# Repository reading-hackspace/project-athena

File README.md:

# Project Athena

A simple project to build and learn electronics and embedded design at rLab

## Objectives:
<ul>
<li>Develop individual and shared electronic design skills</li>
<li>Learn PCB design and build techniques with Kicad and external PCB manufacturers</li>
<li>Improve surface mount and through hole soldering skills</li>
<li>Familiarise members with rLab electronics tools, equipment, and knowledge</li>
<li>Make a fun device</li>
</ul>

## Design Specification
Derived from the previous 555 Synth Punk construction project
<ul>
<li>design should be Microprocessor based rather than 555</li>
<li>It should have a keyboard. This could be buttons, stylophone, touch sensor, or other. Probably single octave.</li>
<li>Cost components and board under £10</li>
<li>Improved Audio output using proper amplifier IC and board mounted speaker, possibly I2S codec</li>
<li>A couple of knobs and buttons to change sound settings</li>
<li>USB powered</li>
<li>Audio output jack</li>
<li>Mixture of surface mount and through hole components</li>
<li>LCD display integral</li> 
<li>Expansion connector to add new personalised features</li>v
<li>C++ or Python programming.</li>
</ul>

## Design Approach
The design is built of modules which can be independently sourced, designed and prototyped before integration into a complete design.

## Proposed Modules
The following modules are proposed to be in the design, being available and at reasonable cost:

### Raspberry Pi Pico Processor Module

The Raspberry Pi Pico module is based on the RP2040 microprocessor. The module includes flash memory, power supply, crystal clock and a USB interface. It is an easy way to to integrate this processor without detail PCB layout and at attractive cost.
The Pi Pico Module have different variants which are pin compatible. They offer different USB Connectors(Micro-B, USB-C), Wireless and bluetooth integrated, and a higher performance version in the RP2350.
[Pi Pico Data sheet](https://datasheets.raspberrypi.com/pico/pico-datasheet.pdf)

The RP2040 is an ARM Cortex M0+ 32 bit processor which operates at 133MHz and includes a wide range of integrated peripherals.
[RP2040 Data sheet](https://datasheets.raspberrypi.com/rp2040/rp2040-datasheet.pdf)

High quality software support for the RP2040 and Pi Pico Modules is available in C/C++ ([C SDK](https://www.raspberrypi.com/documentation/microcontrollers/c_sdk.html), and [Arduino Pi Pico](https://www.tomshardware.com/how-to/program-raspberry-pi-pico-with-arduino-ide)), and Python([Micropython](https://www.raspberrypi.com/documentation/microcontrollers/micropython.html), and [CircuitPython](https://circuitpython.org/board/raspberry_pi_pico/))

### Capacitive touch Music Keyboard

A number of different keyboard switch types were considered including push butttons, stylophone type stylus and capacitive touch. The later was chosen for simplicity and the capability to play chords with multiple notes simultaneously.

A few different alternatives for the capacitive touch keyboard layout and interface were tested. The keyboard was prototyped with copper tape covered in kapton tape to simulate the PCB pads and solder mask in the final PCB. The Pi Pico does support direct connection of GPIO pins to interface capacitive touch switches using the CircuitPython [touchio library](https://docs.circuitpython.org/en/latest/shared-bindings/touchio/index.html), However it uses a lot of GPIO pins for a 12 key keyboard. It was decided to us a specialised Capacitive touch chip with and I2C interface [MPR121](https://www.nxp.com/docs/en/data-sheet/MPR121.pdf). This chip is very small and will present a good challenge in construction, however it is available already mounted on low cost modules for prototyping. The chip supports up to 4 different I2C addresses allowing additional octave to be added.

### PWM Audio Output
The Pi Pico supports PWM output to a GPIO pin for audio tone output. The resulting output is rather noisy as described in section 3.4.1 of the  [RP2040 hardware interface manual](https://datasheets.raspberrypi.com/rp2040/hardware-design-with-rp2040.pdf). It was chosen to implement the low noise 3.3V audio supply, the buffer, and the filter circuit.

### I2S Audio Codec
In addition to the PWM a I2S audio DAC is included for higher quality stereo output. The [PCM5102 DAC](https://www.ti.com/lit/ds/symlink/pcm5102.pdf) analog part is also powered from the low noise 3.3V supply

### Audio Amplifier and Loudspeaker

Low cost audio power amplifiers with 1W output power baaed on the LM386 are available. [LM386 module](https://www.switchelectronics.co.uk/products/lm386-audio-amplifier-board-200-gain-amplifier-module-power)

The LM386 IC can operate with few external components with a gain of 20 which is suitable for our application.[LM386 Data sheet](https://www.ti.com/lit/ds/symlink/lm386.pdf)

The loudspeaker is proposed to be board mounted.[30mm Loudspeaker](https://proto-pic.co.uk/product/speaker-30mm-dia-8-ohm-pcb-mounted)

Audio Output to an external amplifier is provided via a 3.5mm stereo jack.

### 1.3 inch IPS Colour LCD Display

A colour LCD display was chosen for the device. Limited space allows for a [240 by 240 pixel 1.3 inch IPS display](https://www.smart-prototyping.com/1_3-inch-TFT-IPS-Display-Module-ST7789-SPI-240-240).
The module is based on the ST7789 display IC and is supported by both Micropython and CircuitPython grahics libraries.

### Buttons and Potentiometers.

To interact with the device and display, two potentiometers and six push buttons are included.

### General Purpose Inputs and Outputs.

The board provides spare GPIO connections and power supplies on 2.54mm female headers for external experimental devices. The I2c Bus is also brought out to a connectors to daisy chain octaves or add other I2C devices. The connectors can be male or female and mounted vertically or horizontally on the board

##   Estimated Costs
Derived from Kicad BOM. All including VAT and shipping.
<ul>
<li> PCB, 2 layer 100mm * 100mm JLCPCB      £0.75</li>
<li> Pi Pico 2040 module with micro USB     £1.75</li>
<li> 1.3in LCD Display 240 * 240 pixel      £1.75</li>
<li> Integrated circuits                    £1.25</li>
<li> Connectors                             £0.75</li>
<li> Buttons, Potentiometers                £0.50</li>

<li> Resistors, capacitors                  £0.75</li>
</ul>
Total: 

## PCB Files

## Software

The software is in early stage of test and development. The following capabilities have been tested:
<ul>
<li> Display colour rLab logo on LCD display in Circuit Python
<li> SImple one octave piano with output to internal speaker
<li> Polyphonic synthesiser with output via audio codec
<li> Nintendo style games (Tetris, Flappy Bird) with display and sound
<ul>

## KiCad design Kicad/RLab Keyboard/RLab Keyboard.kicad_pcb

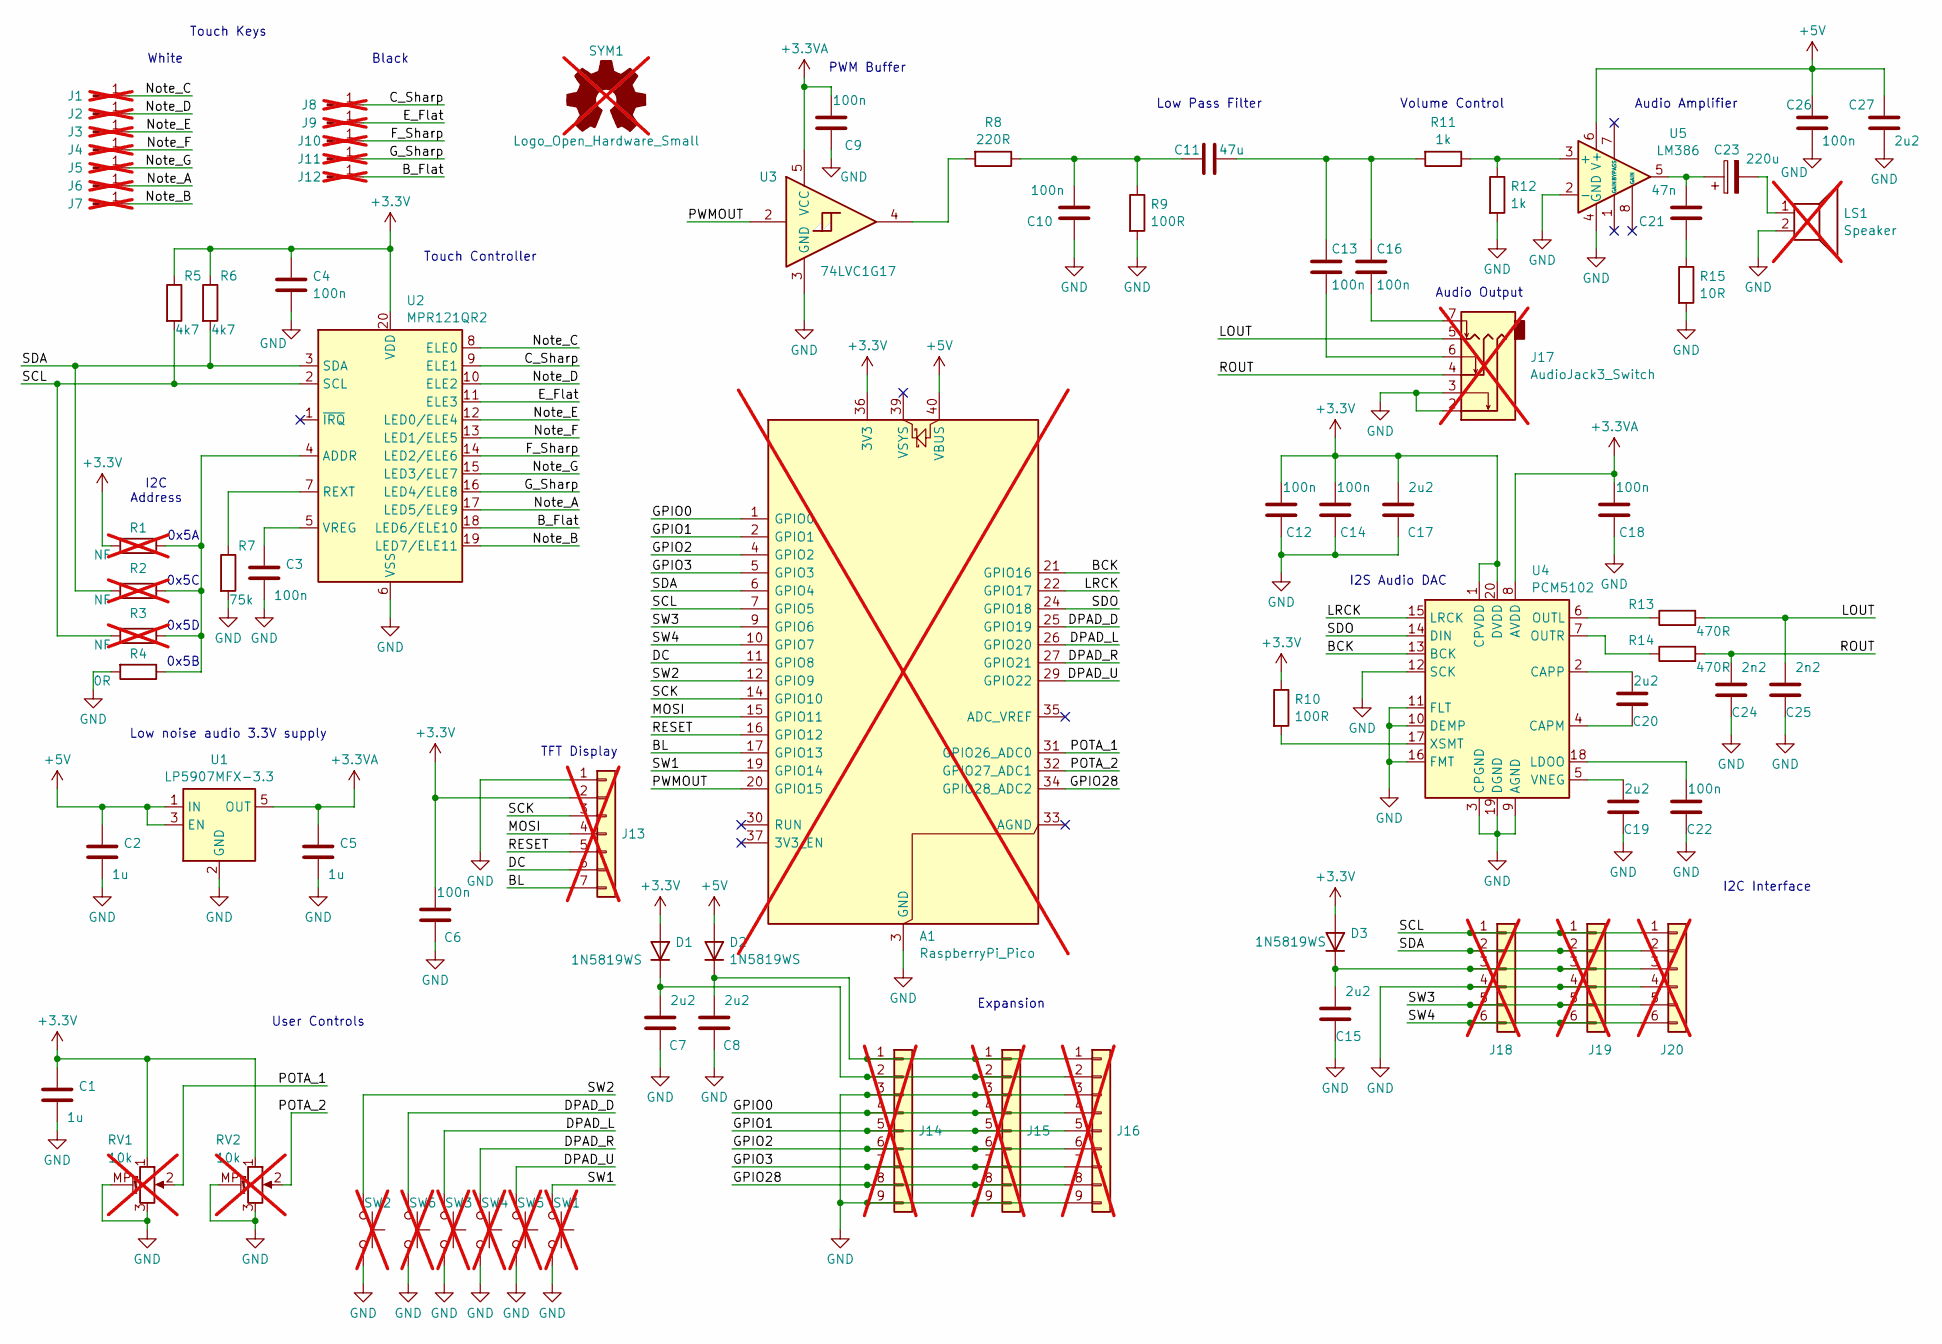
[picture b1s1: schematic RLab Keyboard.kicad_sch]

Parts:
A1: RaspberryPi_Pico; RPi_Pico_SMD_TH; not fitted
C1, C2, C5: 1u; C_0603_1608Metric; LCSC Part C111590
C3, C4, C6, C9, C10, C12, C13, C14, C16, C18, C22, C26: 100n; C_0603_1608Metric; LCSC Part C6119867
C7, C8, C15, C17, C19, C20, C27: 2u2; C_0603_1608Metric; LCSC Part C5189830
C11: 47u; C_0805_2012Metric; LCSC Part C19103846
C21: 47n; C_0603_1608Metric; LCSC Part C597218
C23: 220u; C_1206_3216Metric; LCSC Part C412252
C24, C25: 2n2; C_0603_1608Metric; LCSC Part C1604
D1, D2, D3: 1N5819WS; D_SOD-323; LCSC Part C191023
J1, J2, J3, J4, J5, J6, J7: Conn_01x01_Pin; White_Key; not fitted
J8, J9, J10, J11, J12: Conn_01x01_Pin; Black_key_fill; not fitted
J13: Conn_01x07; 240LCD; not fitted
J14: Conn_01x09; PinHeader_1x09_P2.54mm_Horizontal; not fitted
J15: Conn_01x09; PinSocket_1x09_P2.54mm_Vertical; not fitted
J16: Conn_01x09; PinSocket_1x09_P2.54mm_Horizontal; not fitted
J17: AudioJack3_Switch; Jack_3.5mm_PJ342_Horizontal; LCSC Part C668606; not fitted
J18: Conn_01x06; PinSocket_1x06_P2.54mm_Horizontal; not fitted
J19: Conn_01x06; PinHeader_1x06_P2.54mm_Horizontal; not fitted
J20: Conn_01x06; PinSocket_1x06_P2.54mm_Vertical; not fitted
LS1: Speaker; 30mm_Speaker; not fitted
R1, R2, R3: NF; R_0603_1608Metric; not fitted
R4: 0R; R_0603_1608Metric; LCSC Part C95177
R5, R6: 4k7; R_0603_1608Metric; LCSC Part C99782
R7: 75k; R_0603_1608Metric; LCSC Part C114636
R8: 220R; R_0603_1608Metric; LCSC Part C107696
R9, R10: 100R; R_0603_1608Metric; LCSC Part C105588
R11, R12: 1k; R_0603_1608Metric; LCSC Part C22548
R13, R14: 470R; R_0603_1608Metric; LCSC Part C114669
R15: 10R; R_0603_1608Metric; LCSC Part C22859
RV1, RV2: 10k; Potentiometer_Alps_RK09K_Single_Vertical; not fitted
SW1, SW2, SW3, SW4, SW5, SW6: SW_MEC_5G; SW_PUSH_6mm_H8mm; not fitted
SYM1: Logo_Open_Hardware_Small; OSHW-Logo_11.4x12mm_SilkScreen; not fitted
U1: LP5907MFX-3.3; SOT-23-5; LCSC Part C5370990
U2: MPR121QR2; UQFN-20_3x3mm_P0.4mm; LCSC Part C91322
U3: 74LVC1G17; SOT-353_SC-70-5; LCSC Part C19829654
U4: PCM5102; TSSOP-20_4.4x6.5mm_P0.65mm; LCSC Part C107671
U5: LM386; SOIC-8_3.9x4.9mm_P1.27mm; LCSC Part C22438596

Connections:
+3.3V: A1.36 (3V3), C1.1, C4.1, C6.2, C12.2, C14.2, C17.2, D1.2 (A), D3.2 (A), J13.2, R1.2, R5.1, R6.1, R10.1, RV1.1, RV2.1, U2.20 (VDD), U4.1 (CPVDD), U4.20 (DVDD)
+3.3VA: C5.1, C9.2, C18.2, U1.5 (OUT), U3.5 (VCC), U4.8 (AVDD)
+5V: A1.40 (VBUS), C2.1, C26.1, C27.2, D2.2 (A), U1.1 (IN), U1.3 (EN), U5.6 (V+)
/BCK: A1.21 (GPIO16), U4.13 (BCK)
/BL: A1.17 (GPIO13), J13.7
/B_Flat: J12.1, U2.18 (LED6/ELE10)
/C_Sharp: J8.1, U2.9 (ELE1)
/DC: A1.11 (GPIO8), J13.6
/DPAD_D: A1.25 (GPIO19), SW6.1
/DPAD_L: A1.26 (GPIO20), SW3.1
/DPAD_R: A1.27 (GPIO21), SW4.1
/DPAD_U: A1.29 (GPIO22), SW5.1
/E_Flat: J9.1, U2.11 (ELE3)
/F_Sharp: J10.1, U2.14 (LED2/ELE6)
/GPIO0: A1.1 (GPIO0), J14.4, J15.4, J16.4
/GPIO1: A1.2 (GPIO1), J14.5, J15.5, J16.5
/GPIO2: A1.4 (GPIO2), J14.6, J15.6, J16.6
/GPIO3: A1.5 (GPIO3), J14.7, J15.7, J16.7
/GPIO28: A1.34 (GPIO28_ADC2), J14.8, J15.8, J16.8
/G_Sharp: J11.1, U2.16 (LED4/ELE8)
/LOUT: C25.2, J17.5, R13.2
/LRCK: A1.22 (GPIO17), U4.15 (LRCK)
/MOSI: A1.15 (GPIO11), J13.4
/Note_A: J6.1, U2.17 (LED5/ELE9)
/Note_B: J7.1, U2.19 (LED7/ELE11)
/Note_C: J1.1, U2.8 (ELE0)
/Note_D: J2.1, U2.10 (ELE2)
/Note_E: J3.1, U2.12 (LED0/ELE4)
/Note_F: J4.1, U2.13 (LED1/ELE5)
/Note_G: J5.1, U2.15 (LED3/ELE7)
/POTA_1: A1.31 (GPIO26_ADC0), RV1.2
/POTA_2: A1.32 (GPIO27_ADC1), RV2.2
/PWMOUT: A1.20 (GPIO15), U3.2
/RESET: A1.16 (GPIO12), J13.5
/ROUT: C24.2, J17.4, R14.2
/SCK: A1.14 (GPIO10), J13.3
/SCL: A1.7 (GPIO5), J18.1, J19.1, J20.1, R3.2, R5.2, U2.2 (SCL)
/SDA: A1.6 (GPIO4), J18.2, J19.2, J20.2, R2.2, R6.2, U2.3 (SDA)
/SDO: A1.24 (GPIO18), U4.14 (DIN)
/SW1: A1.19 (GPIO14), SW1.1
/SW2: A1.12 (GPIO9), SW2.1
/SW3: A1.9 (GPIO6), J18.5, J19.5, J20.5
/SW4: A1.10 (GPIO7), J18.6, J19.6, J20.6
GND: A1.3 (GND), A1.8 (GND), A1.13 (GND), A1.18 (GND), A1.23 (GND), A1.28 (GND), A1.38 (GND), C1.2, C2.2, C3.2, C4.2, C5.2, C6.1, C7.1, C8.1, C9.1, C10.1, C12.1, C14.1, C15.1, C17.1, C18.1, C19.1, C22.1, C24.1, C25.1, C26.2, C27.1, J13.1, J14.3, J14.9, J15.3, J15.9, J16.3, J16.9, J17.2, J17.3, J18.4, J19.4, J20.4, LS1.2, R4.2, R7.2, R9.2, R12.2, R15.2, RV1.3, RV1.MP (MountPin), RV2.3, RV2.MP (MountPin), SW1.2, SW2.2, SW3.2, SW4.2, SW5.2, SW6.2, U1.2 (GND), U2.6 (VSS), U3.3 (GND), U4.3 (CPGND), U4.9 (AGND), U4.10 (DEMP), U4.11 (FLT), U4.12 (SCK), U4.16 (FMT), U4.19 (DGND), U5.2 (-), U5.4 (GND)
unnamed: C10.2, C11.2, R8.1, R9.1
unnamed: C11.1, C13.1, C16.1, R11.2
unnamed: C13.2, J17.6
unnamed: C16.2, J17.7
unnamed: C21.1, R15.1
unnamed: C21.2, C23.1, U5.5
unnamed: C23.2, LS1.1
unnamed: C7.2, D1.1 (K), J14.2, J15.2, J16.2
unnamed: C8.2, D2.1 (K), J14.1, J15.1, J16.1
unnamed: C15.2, D3.1 (K), J18.3, J19.3, J20.3
unnamed: R8.2, U3.4
unnamed: R1.1, R2.1, R3.1, R4.1, U2.4 (ADDR)
unnamed: R7.1, U2.7 (REXT)
unnamed: C3.1, U2.5 (VREG)
unnamed: C20.1, U4.4 (CAPM)
unnamed: C20.2, U4.2 (CAPP)
unnamed: C22.2, U4.18 (LDOO)
unnamed: R13.1, U4.6 (OUTL)
unnamed: R14.1, U4.7 (OUTR)
unnamed: C19.2, U4.5 (VNEG)
unnamed: R10.2, U4.17 (XSMT)
unnamed: R11.1, R12.1, U5.3 (+)

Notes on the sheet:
PWM Buffer
Black
I2C Address
Touch Keys
Audio Amplifier
0x5C
0x5A
Audio Output
0x5B
TFT Display
Low noise audio 3.3V supply
Volume Control
Low Pass Filter
I2C Interface
Expansion
0x5D
I2S Audio DAC
User Controls
Touch Controller
White

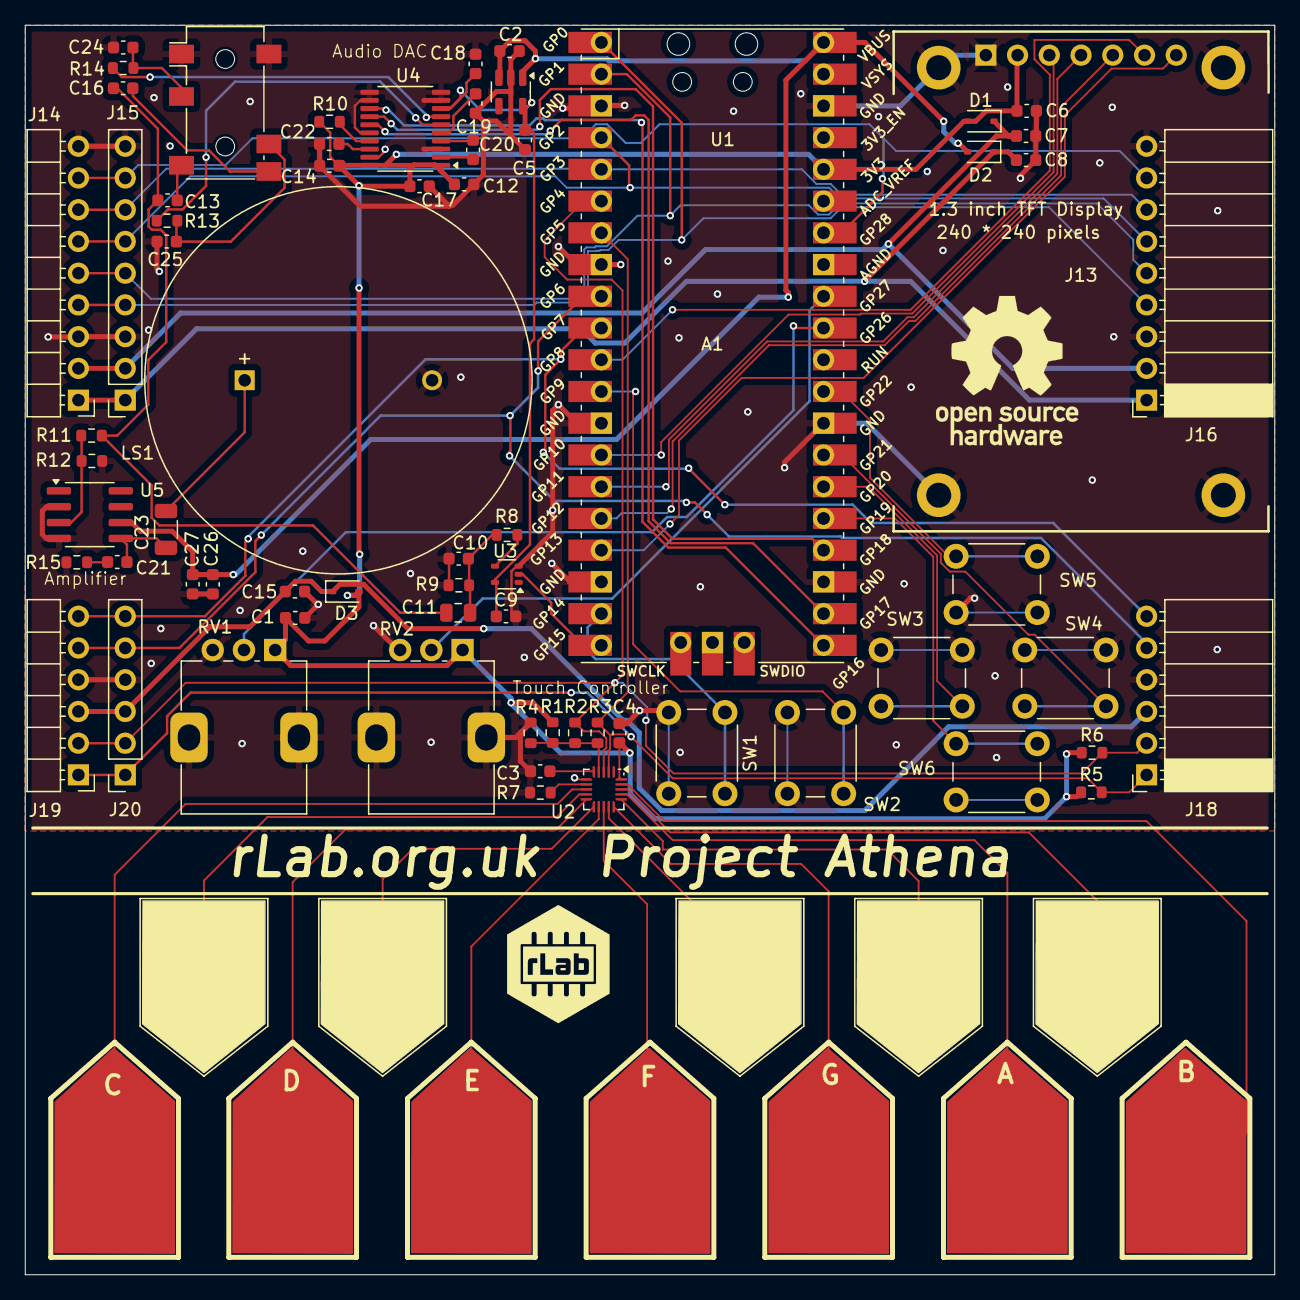
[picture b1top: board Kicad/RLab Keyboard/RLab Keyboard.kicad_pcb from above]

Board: 2 copper layers, 100.0 x 100.0 mm, 81 parts (0 on the bottom side), 66 nets.

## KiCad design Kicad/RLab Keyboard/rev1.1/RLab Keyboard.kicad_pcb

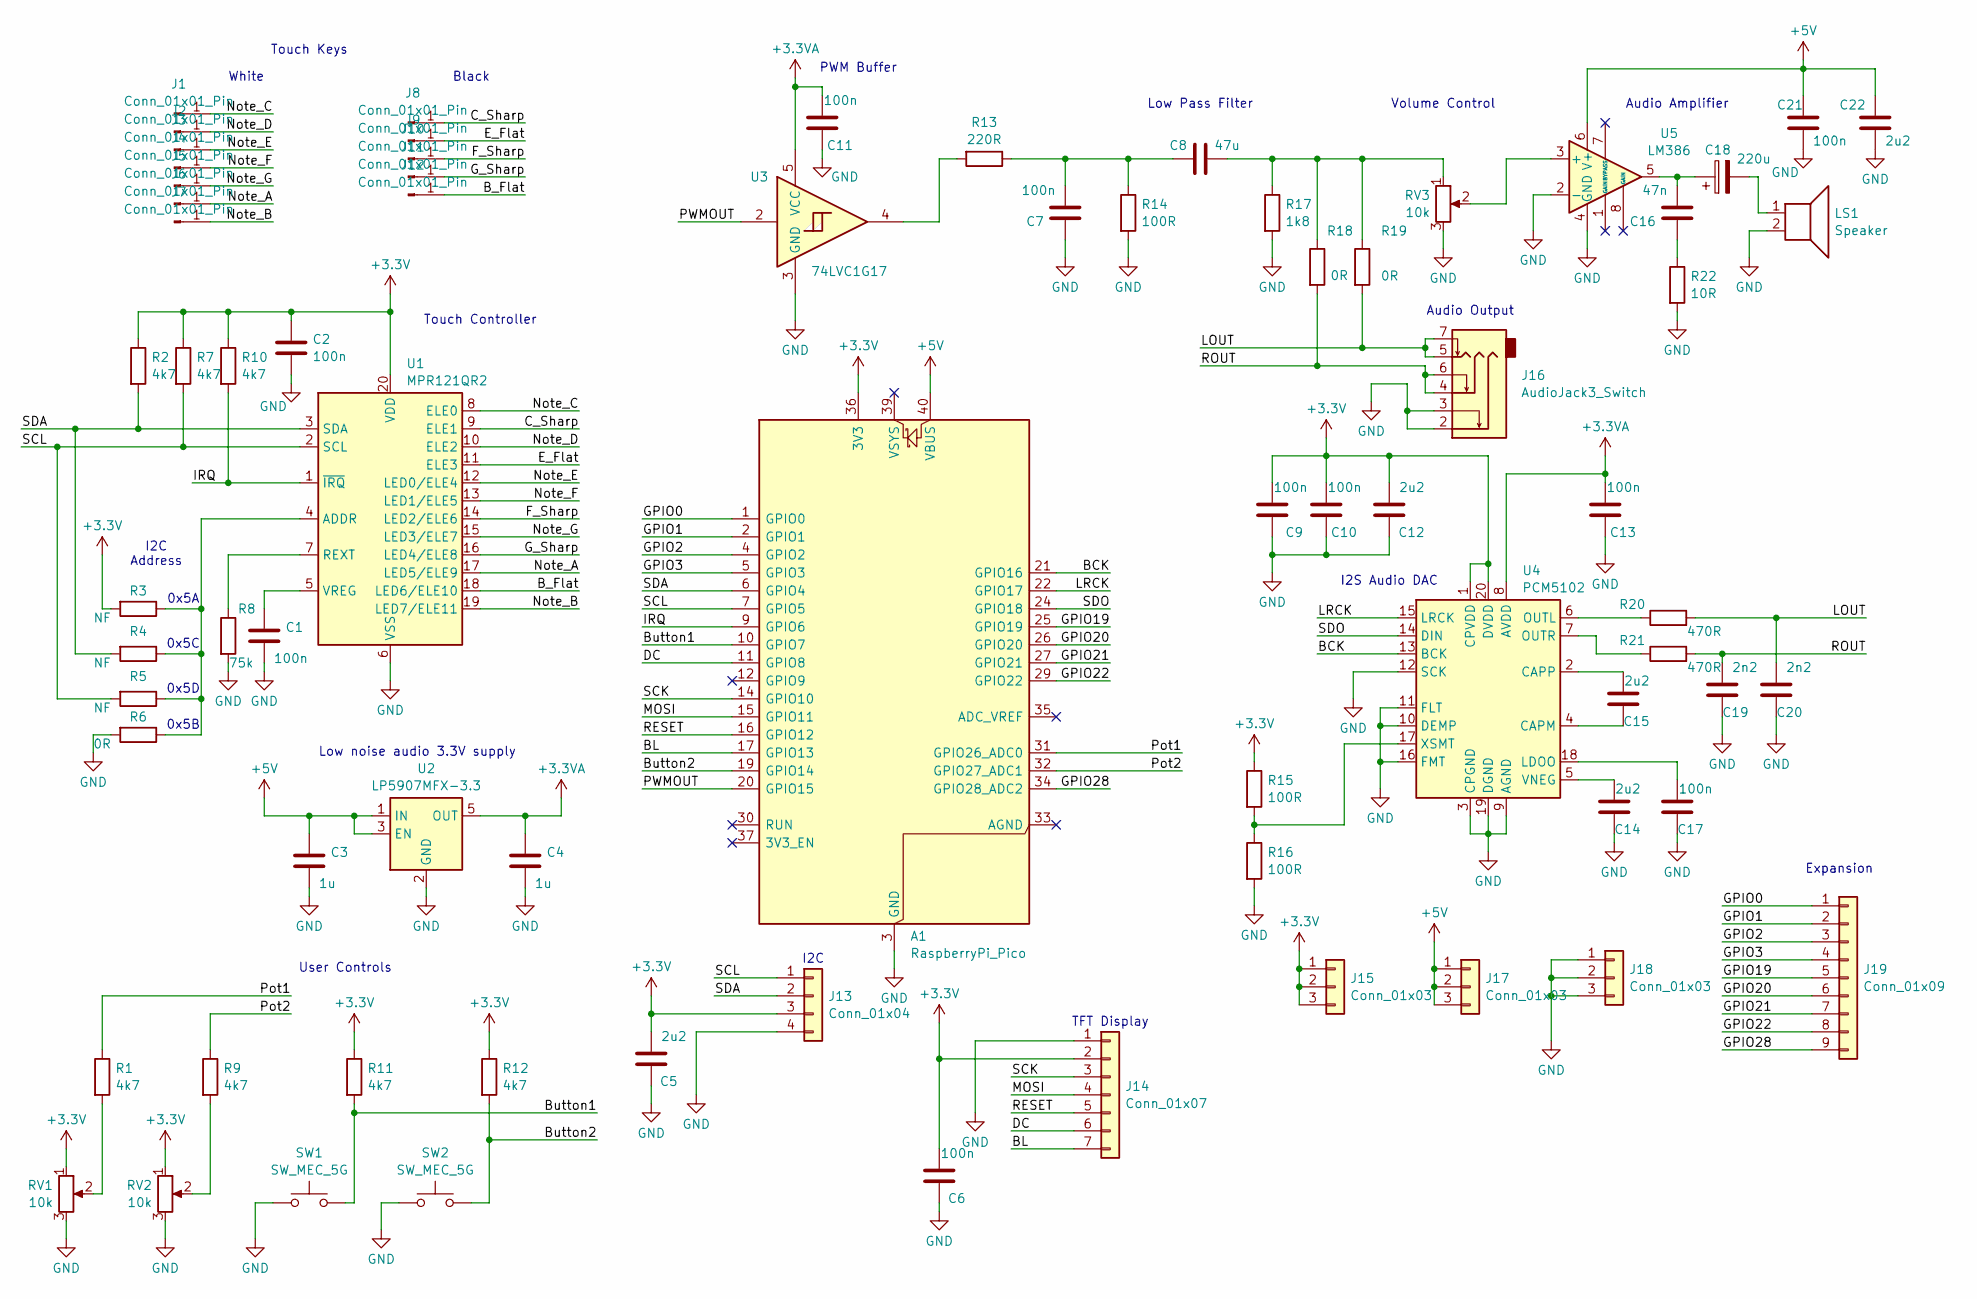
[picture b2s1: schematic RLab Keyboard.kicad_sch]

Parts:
A1: RaspberryPi_Pico; RPi_Pico_SMD_TH
C1, C2, C6, C7, C9, C10, C11, C13, C17, C21: 100n; C_0603_1608Metric
C3, C4: 1u; C_0603_1608Metric
C5, C12, C14, C15, C22: 2u2; C_0603_1608Metric
C8: 47u; C_0805_2012Metric
C16: 47n; C_0603_1608Metric
C18: 220u; C_1206_3216Metric
C19, C20: 2n2; C_0603_1608Metric
J1, J2, J3, J4, J5, J6, J7: Conn_01x01_Pin; White_Key
J8, J9, J10, J11, J12: Conn_01x01_Pin; Black_key_fill
J13: Conn_01x04; PinSocket_1x04_P2.54mm_Vertical
J14: Conn_01x07; 240LCD
J15, J17, J18: Conn_01x03; PinSocket_1x03_P2.54mm_Vertical
J16: AudioJack3_Switch; Jack_3.5mm_PJ342_Horizontal
J19: Conn_01x09; PinSocket_1x09_P2.54mm_Vertical
LS1: Speaker; 30mm_Speaker
R1, R2, R7, R9, R10, R11, R12: 4k7; R_0603_1608Metric
R3, R4, R5: NF; R_0603_1608Metric
R6, R18, R19: 0R; R_0603_1608Metric
R8: 75k; R_0603_1608Metric
R13: 220R; R_0603_1608Metric
R14, R15, R16: 100R; R_0603_1608Metric
R17: 1k8; R_0603_1608Metric
R20, R21: 470R; R_0603_1608Metric
R22: 10R; R_0603_1608Metric
RV1, RV2: 10k; Potentiometer_Alps_RK09K_Single_Vertical
RV3: 10k; Potentiometer_Bourns_3214G_Horizontal
SW1, SW2: SW_MEC_5G; SW_PUSH_6mm_H5mm
U1: MPR121QR2; UQFN-20_3x3mm_P0.4mm
U2: LP5907MFX-3.3; SOT-23-5
U3: 74LVC1G17; SOT-353_SC-70-5
U4: PCM5102; TSSOP-20_4.4x6.5mm_P0.65mm
U5: LM386; SOIC-8_3.9x4.9mm_P1.27mm

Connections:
+3.3V: A1.36 (3V3), C2.1, C5.2, C6.2, C9.2, C10.2, C12.2, J13.3, J14.2, J15.1, J15.2, J15.3, R2.1, R3.2, R7.1, R10.1, R11.1, R12.1, R15.1, RV1.1, RV2.1, U1.20 (VDD), U4.1 (CPVDD), U4.20 (DVDD)
+3.3VA: C4.1, C11.2, C13.2, U2.5 (OUT), U3.5 (VCC), U4.8 (AVDD)
+5V: A1.40 (VBUS), C3.1, C21.1, C22.2, J17.1, J17.2, J17.3, U2.1 (IN), U2.3 (EN), U5.6 (V+)
/BCK: A1.21 (GPIO16), U4.13 (BCK)
/BL: A1.17 (GPIO13), J14.7
/B_Flat: J12.1, U1.18 (LED6/ELE10)
/Button1: A1.10 (GPIO7), R11.2, SW1.2
/Button2: A1.19 (GPIO14), R12.2, SW2.2
/C_Sharp: J8.1, U1.9 (ELE1)
/DC: A1.11 (GPIO8), J14.6
/E_Flat: J9.1, U1.11 (ELE3)
/F_Sharp: J10.1, U1.14 (LED2/ELE6)
/GPIO0: A1.1 (GPIO0), J19.1
/GPIO1: A1.2 (GPIO1), J19.2
/GPIO2: A1.4 (GPIO2), J19.3
/GPIO3: A1.5 (GPIO3), J19.4
/GPIO19: A1.25 (GPIO19), J19.5
/GPIO20: A1.26 (GPIO20), J19.6
/GPIO21: A1.27 (GPIO21), J19.7
/GPIO22: A1.29 (GPIO22), J19.8
/GPIO28: A1.34 (GPIO28_ADC2), J19.9
/G_Sharp: J11.1, U1.16 (LED4/ELE8)
/IRQ: A1.9 (GPIO6), R10.2, U1.1 (~IRQ)
/LOUT: C20.2, J16.5, J16.7, R19.2, R20.2
/LRCK: A1.22 (GPIO17), U4.15 (LRCK)
/MOSI: A1.15 (GPIO11), J14.4
/Note_A: J6.1, U1.17 (LED5/ELE9)
/Note_B: J7.1, U1.19 (LED7/ELE11)
/Note_C: J1.1, U1.8 (ELE0)
/Note_D: J2.1, U1.10 (ELE2)
/Note_E: J3.1, U1.12 (LED0/ELE4)
/Note_F: J4.1, U1.13 (LED1/ELE5)
/Note_G: J5.1, U1.15 (LED3/ELE7)
/PWMOUT: A1.20 (GPIO15), U3.2
/Pot1: A1.31 (GPIO26_ADC0), R1.1
/Pot2: A1.32 (GPIO27_ADC1), R9.1
/RESET: A1.16 (GPIO12), J14.5
/ROUT: C19.2, J16.4, J16.6, R18.2, R21.2
/SCK: A1.14 (GPIO10), J14.3
/SCL: A1.7 (GPIO5), J13.1, R5.2, R7.2, U1.2 (SCL)
/SDA: A1.6 (GPIO4), J13.2, R2.2, R4.2, U1.3 (SDA)
/SDO: A1.24 (GPIO18), U4.14 (DIN)
GND: A1.3 (GND), A1.8 (GND), A1.13 (GND), A1.18 (GND), A1.23 (GND), A1.28 (GND), A1.38 (GND), C1.2, C2.2, C3.2, C4.2, C5.1, C6.1, C7.1, C9.1, C10.1, C11.1, C12.1, C13.1, C14.1, C17.1, C19.1, C20.1, C21.2, C22.1, J13.4, J14.1, J16.2, J16.3, J18.1, J18.2, J18.3, LS1.2, R6.2, R8.2, R14.2, R16.2, R17.2, R22.2, RV1.3, RV2.3, RV3.3, SW1.1, SW2.1, U1.6 (VSS), U2.2 (GND), U3.3 (GND), U4.3 (CPGND), U4.9 (AGND), U4.10 (DEMP), U4.11 (FLT), U4.12 (SCK), U4.16 (FMT), U4.19 (DGND), U5.2 (-), U5.4 (GND)
unnamed: C7.2, C8.2, R13.1, R14.1
unnamed: C8.1, R17.1, R18.1, R19.1, RV3.1
unnamed: C16.1, R22.1
unnamed: C16.2, C18.1, U5.5
unnamed: C18.2, LS1.1
unnamed: R1.2, RV1.2
unnamed: R9.2, RV2.2
unnamed: R13.2, U3.4
unnamed: R3.1, R4.1, R5.1, R6.1, U1.4 (ADDR)
unnamed: R8.1, U1.7 (REXT)
unnamed: C1.1, U1.5 (VREG)
unnamed: C15.1, U4.4 (CAPM)
unnamed: C15.2, U4.2 (CAPP)
unnamed: C17.2, U4.18 (LDOO)
unnamed: R20.1, U4.6 (OUTL)
unnamed: R21.1, U4.7 (OUTR)
unnamed: C14.2, U4.5 (VNEG)
unnamed: R15.2, R16.1, U4.17 (XSMT)
unnamed: RV3.2, U5.3 (+)

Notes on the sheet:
PWM Buffer
Black
I2C Address
Touch Keys
Audio Amplifier
0x5C
0x5A
Audio Output
0x5B
TFT Display
Low noise audio 3.3V supply
Volume Control
Low Pass Filter
I2C
Expansion
0x5D
I2S Audio DAC
User Controls
Touch Controller
White

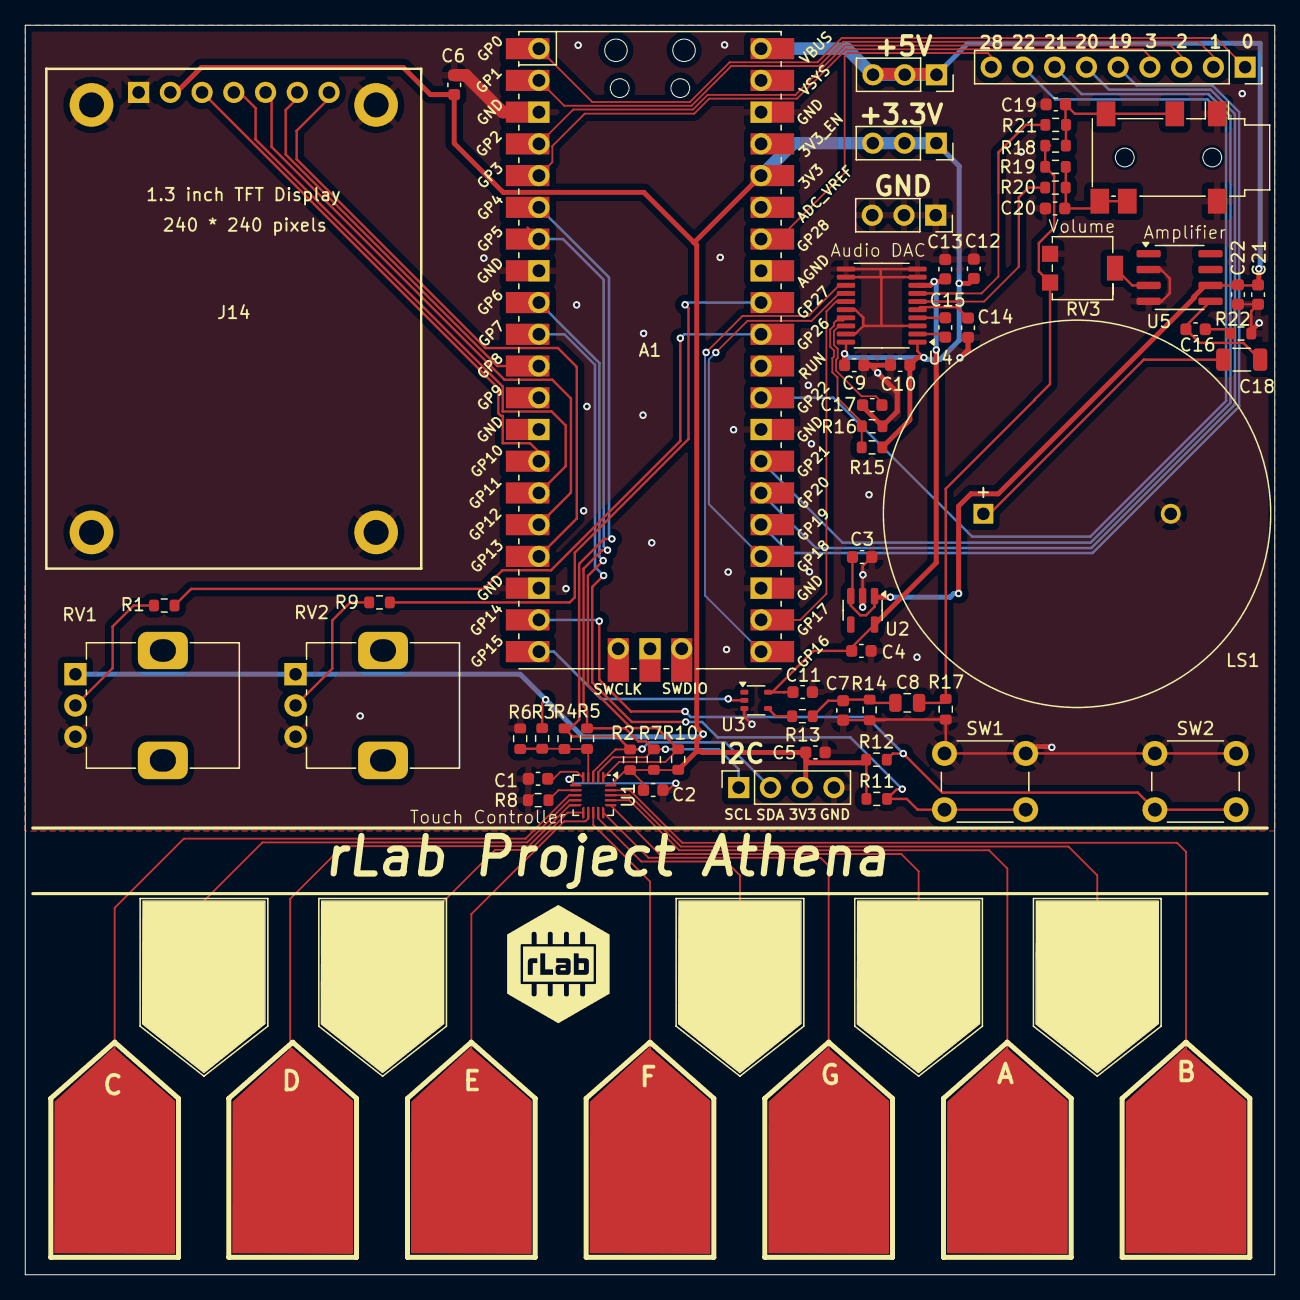
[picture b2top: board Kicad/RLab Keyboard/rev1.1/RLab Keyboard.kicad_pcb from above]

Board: 2 copper layers, 100.0 x 100.0 mm, 75 parts (0 on the bottom side), 62 nets.

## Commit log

2024-09-07 Updateing formating
2024-09-11 Added Kicad files and updated README.md
    First post of Kicad files for prototype
    Update README.md to give detailed project description
2024-09-11 Update Gerbers
    Update Gerber files and BOM
2024-09-11 Added CircuitPython and Micropython files
2024-09-27 Added workflow to validate and generate fabrication files, etc
2024-09-27 Quote the file names as they have spaces
2024-09-27 Updated action versions to fix warnings
2024-09-27 A few more corrections to workflow
2024-09-27 Initial submit of version 1.2
    Update to layout of Kicad files for new user interface
    Added circuit Python test firmware
2024-09-28 Fix fabrication action
2024-09-28 Generate 3D printable stencil files
2024-10-02 Remove locks on Kicad files
    Remove lock on rLab Keyboard Kicad .sch and .pcb
2024-11-01 Latest rLab Keyboard layout
    Added connectors for joining boards
    Swap display and speaker.
    New control layout
2024-11-05 Add games to Micropython directory
2024-11-05 Fix DRC issues in latest KiCAD
2024-11-05 Warning fisex
2024-11-07 Files updated for JLCPCB Assembly
    Added DNP for through hole components. can be viewed as option in 3D viewer.
    Production files in JLCPCB folder
2024-11-29 Update README.md
    Update 3D image
